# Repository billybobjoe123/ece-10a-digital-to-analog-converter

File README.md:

# ece-10a-digital-to-analog-converter
Designed a digital to analog converter in kicad

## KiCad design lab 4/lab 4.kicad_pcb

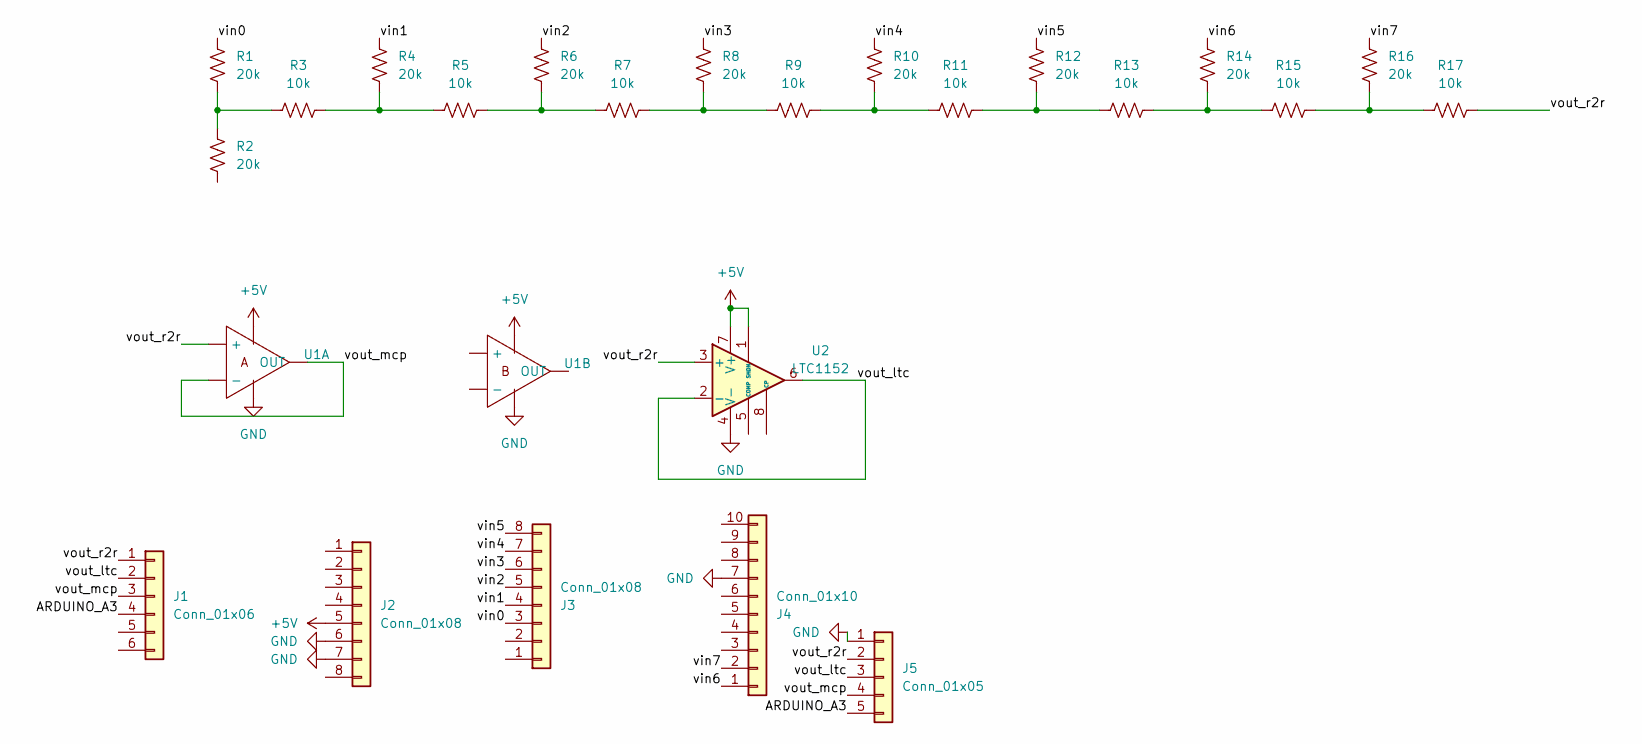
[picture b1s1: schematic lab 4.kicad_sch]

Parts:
J1: Conn_01x06; PinHeader_1x06_P2.54mm_Vertical
J2, J3: Conn_01x08; PinHeader_1x08_P2.54mm_Vertical
J4: Conn_01x10; PinHeader_1x10_P2.54mm_Vertical
J5: Conn_01x05; PinHeader_1x05_P2.54mm_Vertical
R1, R2, R4, R6, R8, R10, R12, R14, R16: 20k; R_Axial_DIN0207_L6.3mm_D2.5mm_P10.16mm_Horizontal
R3, R5, R7, R9, R11, R13, R15, R17: 10k; R_Axial_DIN0207_L6.3mm_D2.5mm_P10.16mm_Horizontal
U1: SOIC-8
U2: LTC1152; SOIC-8_3.9x4.9mm_P1.27mm

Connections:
+5V: J2.5, U1.8 (VDD), U2.1 (SHDN), U2.7 (V+)
/ARDUINO_A3: J1.4, J5.5
/vin0: J3.3, R1.1
/vin1: J3.4, R4.1
/vin2: J3.5, R6.1
/vin3: J3.6, R8.1
/vin4: J3.7, R10.1
/vin5: J3.8, R12.1
/vin6: J4.1, R14.1
/vin7: J4.2, R16.1
/vout_ltc: J1.2, J5.3, U2.2 (-), U2.6
/vout_mcp: J1.3, J5.4, U1.1 (OUT), U1.2 (-)
/vout_r2r: J1.1, J5.2, R17.2, U1.3 (+), U2.3 (+)
GND: J2.6, J2.7, J4.7, J5.1, U1.4 (VSS), U2.4 (V-)
unnamed: R1.2, R2.1, R3.1
unnamed: R3.2, R4.2, R5.1
unnamed: R5.2, R6.2, R7.1
unnamed: R7.2, R8.2, R9.1
unnamed: R9.2, R10.2, R11.1
unnamed: R11.2, R12.2, R13.1
unnamed: R13.2, R14.2, R15.1
unnamed: R15.2, R16.2, R17.1

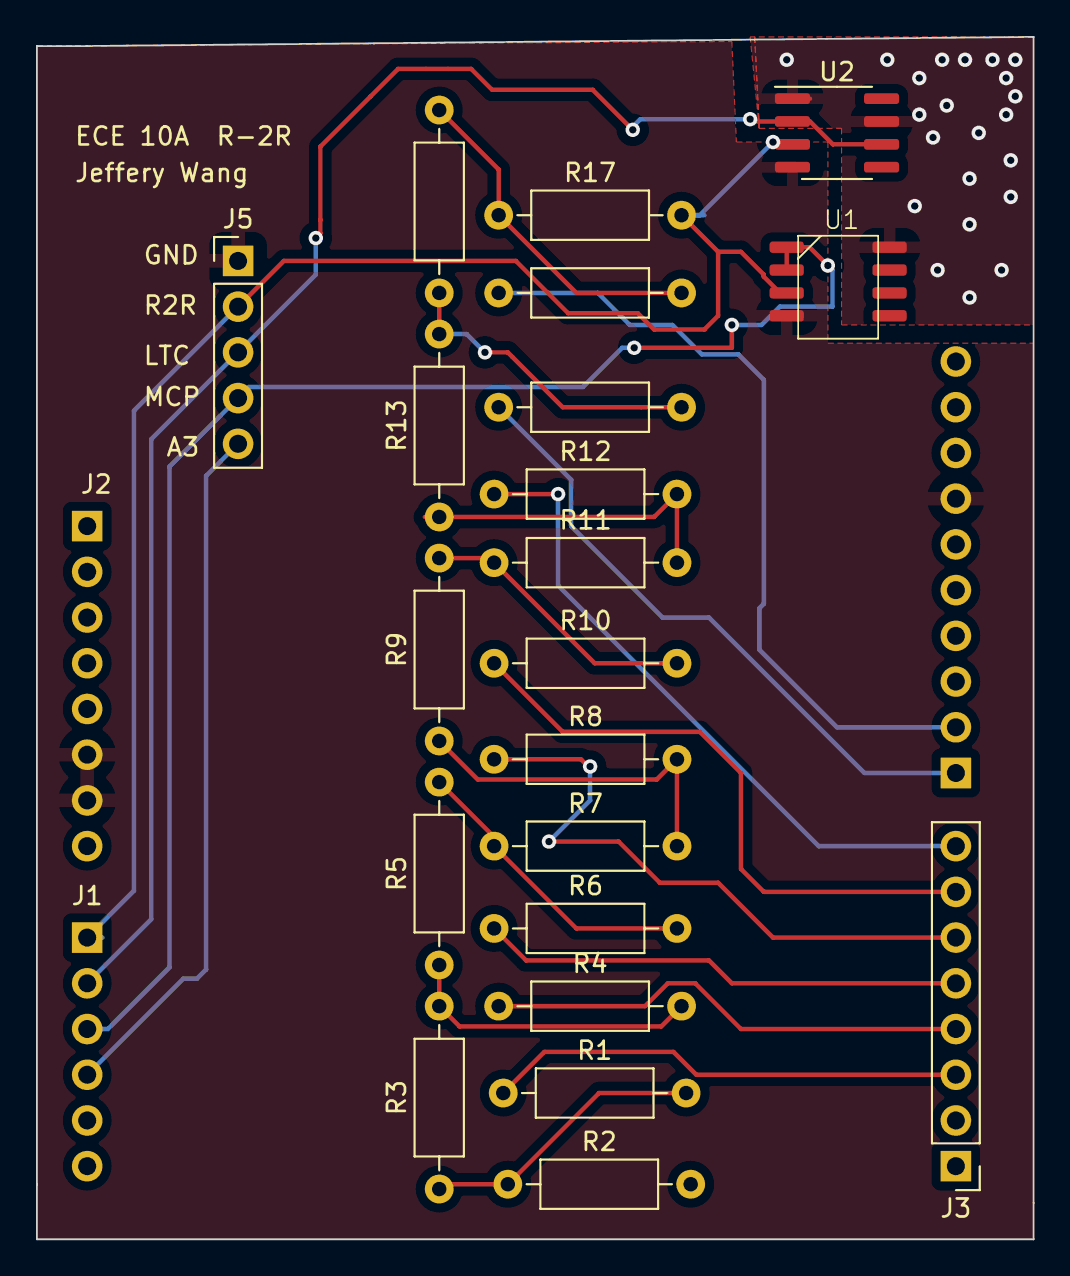
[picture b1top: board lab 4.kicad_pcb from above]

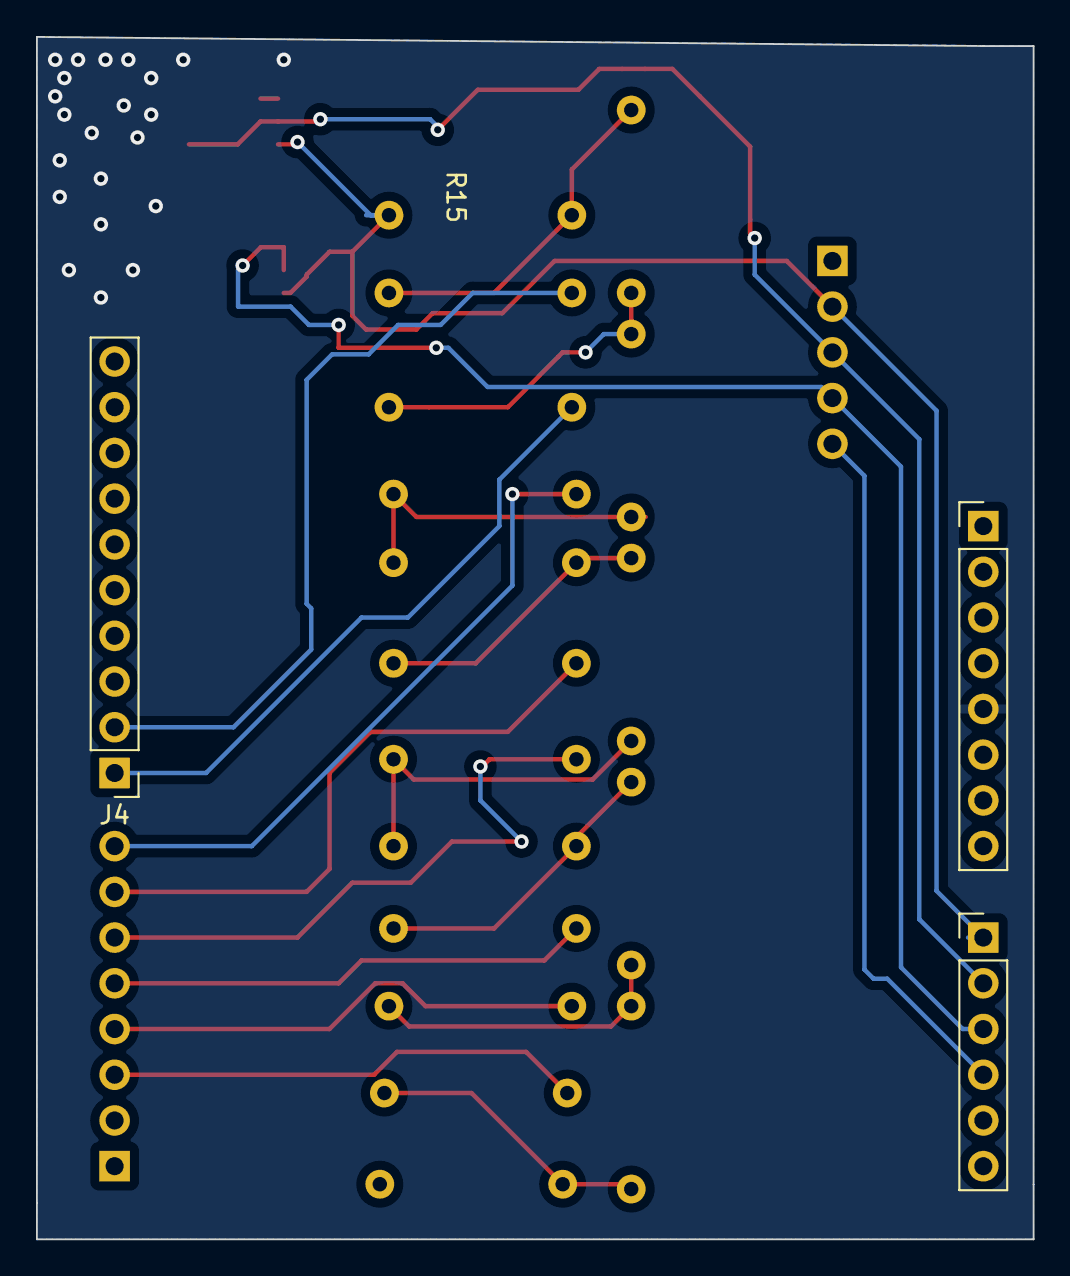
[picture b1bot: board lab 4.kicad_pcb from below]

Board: 2 copper layers, 55.4 x 66.8 mm, 24 parts (3 on the bottom side), 22 nets.
